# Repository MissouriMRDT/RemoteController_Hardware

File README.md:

# RemoteController_Hardware (Rev2_BuildTest)
This branch is for testing a new revision 2 build that removes the nodeMCU development board in place of a standalone ESP-12E, and replaces the LCD screen for an OLED.

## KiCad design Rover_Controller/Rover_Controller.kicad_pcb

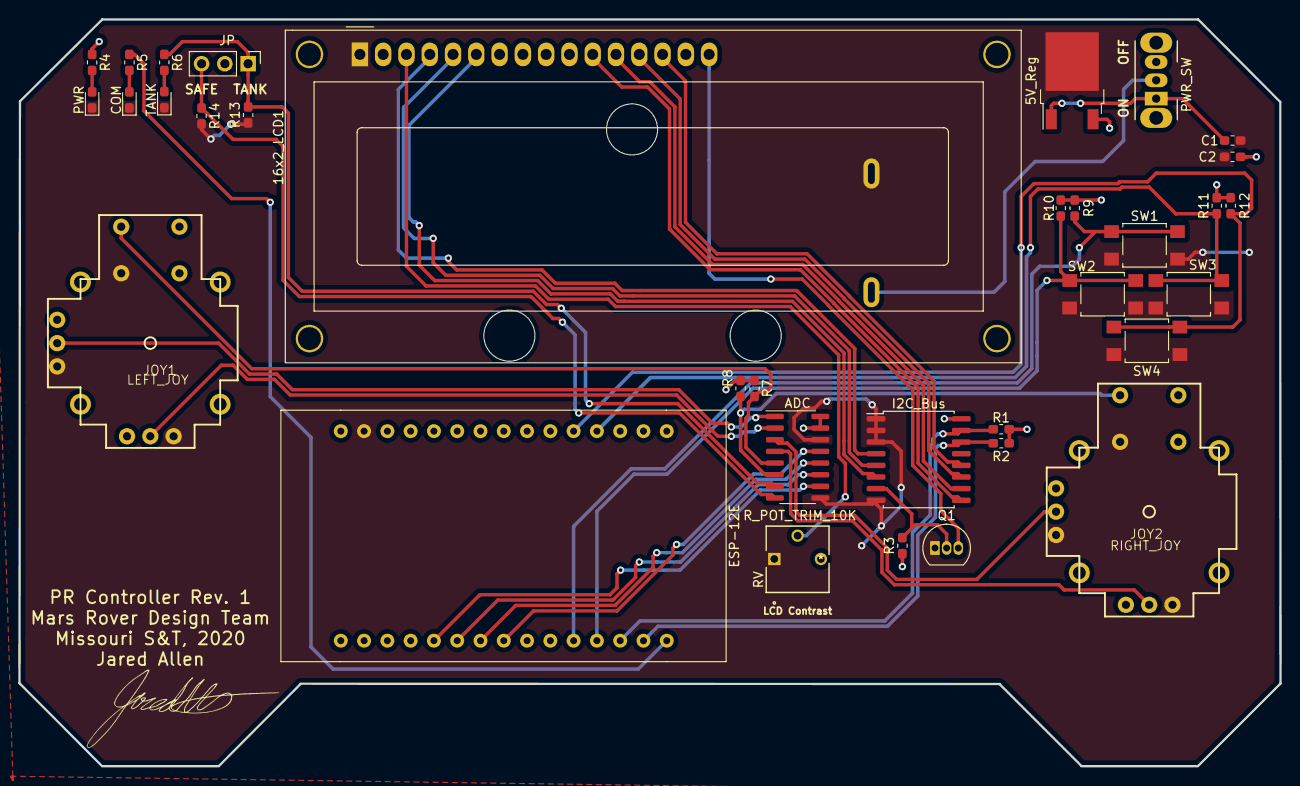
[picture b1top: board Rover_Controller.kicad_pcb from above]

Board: 2 copper layers, 137.6 x 81.5 mm, 35 parts (1 on the bottom side), 36 nets.

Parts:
5V_Reg: L7805; TO-252-2
16x2_LCD1: RC1602A; WC1602A
ADC: MCP3008; SOIC-16_3.9x9.9mm_P1.27mm
BT1: 9V_BAT; Battery_Holder_9V_BC9VPC-ND
C1, C2: 1uF; C_0603_1608Metric_Pad1.05x0.95mm_HandSolder
COM: BLUE; LED_0603_1608Metric_Pad1.05x0.95mm_HandSolder
ESP-12E: ESP8266_NodeMCU; ESP8266_nodeMCU
I2C_Bus: PCF8574; SOIC-16W_7.5x10.3mm_P1.27mm
JOY1: LEFT_JOY; JOYSTICK
JOY2: RIGHT_JOY; JOYSTICK
JP: Jumper_NC_Dual; PinHeader_1x03_P2.54mm_Vertical
PWR: GREEN; LED_0603_1608Metric_Pad1.05x0.95mm_HandSolder
PWR_SW: SW_SPDT; SW_CuK_OS102011MA1QN1_SPDT_Angled
Q1: S8050; TO-92_Inline
R1, R2, R3: 4.7K; R_0603_1608Metric_Pad1.05x0.95mm_HandSolder
R4, R5, R6: 510; R_0603_1608Metric_Pad1.05x0.95mm_HandSolder
R7, R8, R9, R10, R11, R12, R13, R14: 10K; R_0603_1608Metric_Pad1.05x0.95mm_HandSolder
RV: R_POT_TRIM_10K; 3362P-1-103LF
SW1, SW2, SW3, SW4: SW_Push; SW_SPST_TL3305A
TANK: RED; LED_0603_1608Metric_Pad1.05x0.95mm_HandSolder

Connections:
+5V: 5V_Reg.3, 16x2_LCD1.2, 16x2_LCD1.15, ADC.15, ADC.16, C2.1, ESP-12E.29, I2C_Bus.16, JOY1.H1, JOY1.V1, JOY2.H1, JOY2.V1, JP.2, R1.1, R2.1, R3.1, R4.1, R7.1, R8.1, R9.2, R10.2, R11.2, R12.2, RV.3
CLK: ADC.13, ESP-12E.16
CS: ADC.10, ESP-12E.22
D0: ESP-12E.2, R5.1
Din: ADC.11, ESP-12E.20
Dout: ADC.12, ESP-12E.18
GND: 5V_Reg.2, 16x2_LCD1.1, ADC.9, ADC.14, BT1.2, C1.2, C2.2, COM.1, ESP-12E.27, I2C_Bus.1, I2C_Bus.2, I2C_Bus.3, I2C_Bus.8, JOY1.B2A, JOY1.H3, JOY1.V3, JOY2.B2A, JOY2.H3, JOY2.V3, PWR.1, Q1.1, R13.1, R14.2, RV.1, SW1.2, SW2.2, SW3.2, SW4.2, TANK.1
LeftHorz: ADC.2, JOY1.H2
LeftSel: ADC.5, JOY1.B1A, R7.2
LeftVert: ADC.1, JOY1.V2
unnamed: 5V_Reg.1, C1.1, PWR_SW.1
unnamed: 16x2_LCD1.4, I2C_Bus.4
unnamed: 16x2_LCD1.5, I2C_Bus.5
unnamed: 16x2_LCD1.6, I2C_Bus.6
unnamed: 16x2_LCD1.11, I2C_Bus.9
unnamed: 16x2_LCD1.12, I2C_Bus.10
unnamed: 16x2_LCD1.13, I2C_Bus.11
unnamed: 16x2_LCD1.14, I2C_Bus.12
unnamed: BT1.1, PWR_SW.2
unnamed: COM.2, R5.2
unnamed: PWR.2, R4.2
unnamed: R6.2, TANK.2
P3: I2C_Bus.7, Q1.2, R3.2
RightHorz: ADC.4, JOY2.H2
RightSel: ADC.6, JOY2.B1A, R8.2
RightVert: ADC.3, JOY2.V2
SCL: ESP-12E.4, I2C_Bus.14, R2.2
SDA: ESP-12E.6, I2C_Bus.15, R1.2
SW1: ESP-12E.10, R9.1, SW1.1
SW2: ESP-12E.8, R10.1, SW2.1
SW3: ESP-12E.7, R11.1, SW3.1
SW4: ESP-12E.9, R12.1, SW4.1
SafeDrive: ADC.8, JP.3, R14.1
TankDrive: ADC.7, JP.1, R6.1, R13.2
V0: 16x2_LCD1.3, RV.2
k: 16x2_LCD1.16, Q1.3

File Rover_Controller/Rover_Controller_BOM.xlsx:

Id | Designator | Package | Quantity | Designation | Item Name | Part Number | Vendor | Cost Per Item | Cost | URL | Comments | Quantity
1 | R10,R7,R8,R12,R11,R9,R13,R14 | R_0603_1608Metric_Pad1.05x0.95mm_HandSolder | 8 | 10K |  |  |  |  |  |  |  |  |  | Total Cost
2 | BT1 | Battery_Holder_9V_BC9VPC-ND | 1 | 9V_BAT |  |  |  |  |  |  |  |  |  | 0
3 | R6,R5,R4 | R_0603_1608Metric_Pad1.05x0.95mm_HandSolder | 3 | 510
4 | I2C_Bus1 | SOIC-16W_7.5x10.3mm_P1.27mm | 1 | PCF8574
5 | R1,R2,R3 | R_0603_1608Metric_Pad1.05x0.95mm_HandSolder | 3 | 4.7K
6 | C2,C1 | C_0603_1608Metric_Pad1.05x0.95mm_HandSolder | 2 | 1uF
7 | ADC1 | SOIC-16_3.9x9.9mm_P1.27mm | 1 | MCP3008
8 | COM1 | LED_0603_1608Metric_Pad1.05x0.95mm_HandSolder | 1 | BLUE
9 | TANK1 | LED_0603_1608Metric_Pad1.05x0.95mm_HandSolder | 1 | RED
10 | JP1 | PinHeader_1x03_P2.54mm_Vertical | 1 | Jumper_NC_Dual
11 | 16x2_LCD1 | WC1602A | 1 | RC1602A
12 | JOY2 | JOYSTICK | 1 | RIGHT_JOY
13 | Q1 | TO-92_Inline | 1 | S8050
14 | JOY1 | JOYSTICK | 1 | LEFT_JOY
15 | ESP-12E1 | ESP8266_nodeMCU | 1 | ESP8266_NodeMCU
16 | PWR1 | LED_0603_1608Metric_Pad1.05x0.95mm_HandSolder | 1 | GREEN
17 | RV1 | 3362P-1-103LF | 1 | R_POT_TRIM_10K
18 | SW1,SW2,SW3,SW4 | SW_SPST_TL3305A | 4 | SW_Push
19 | PWR_SW1 | SW_CuK_OS102011MA1QN1_SPDT_Angled | 1 | SW_SPDT
20 | 5V_Reg_1 | TO-252-2 | 1 | L7805

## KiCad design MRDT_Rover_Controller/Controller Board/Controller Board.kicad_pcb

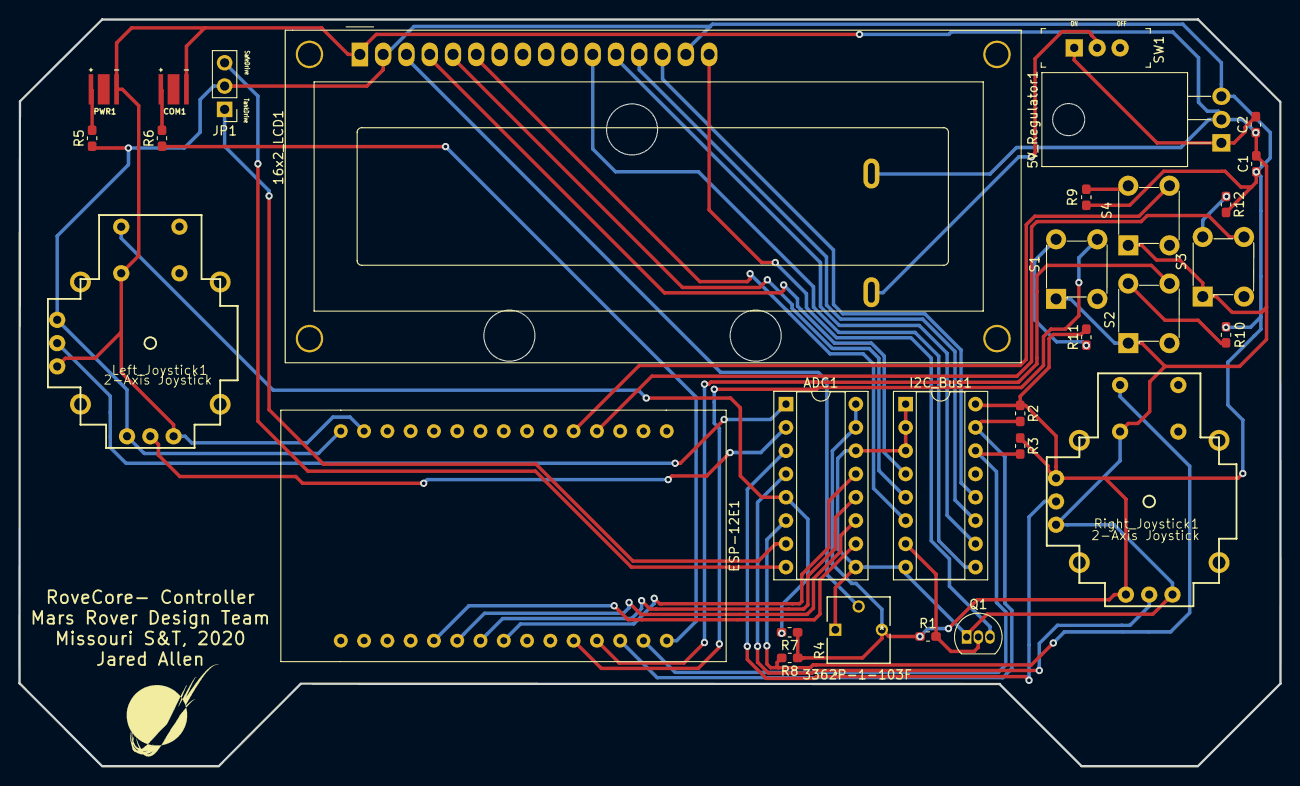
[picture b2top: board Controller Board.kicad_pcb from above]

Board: 2 copper layers, 137.6 x 81.5 mm, 31 parts (1 on the bottom side), 39 nets.

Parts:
5V_Regulator1: L7805; TO-220-3_Horizontal_TabDown
16x2_LCD1: RC1602A; WC1602A
ADC1: MCP3008; DIP-16_W7.62mm_Socket
BAT1: BC9VPC; Battery_Holder_9V_BC9VPC-ND
C1, C2: 1uF; C_0603_1608Metric_Pad1.05x0.95mm_HandSolder
COM1: BLUE; LED_CREE_XLAMP_XPG
ESP-12E1: ESP8266_NodeMCU; ESP8266_nodeMCU
I2C_Bus1: PCF8574; DIP-16_W7.62mm_Socket
JP1: Jumper_NC_Dual; PinHeader_1x03_P2.54mm_Vertical
Left_Joystick1: 2-Axis Joystick; JOYSTICK
PWR1: GREEN; LED_CREE_XLAMP_XPG
Q1: S8050; TO-92_Inline
R1, R2, R3: 4.7K; R_0603_1608Metric_Pad1.05x0.95mm_HandSolder
R4: 3362P-1-103F; 3362P-1-103LF
R5, R6: 100; R_0603_1608Metric_Pad1.05x0.95mm_HandSolder
R7, R8: 1K; R_0603_1608Metric_Pad1.05x0.95mm_HandSolder
R9, R10, R11, R12: 10K; R_0603_1608Metric_Pad1.05x0.95mm_HandSolder
Right_Joystick1: 2-Axis Joystick; JOYSTICK
S1, S2, S3, S4: 1825910-6; Switch_Tactile_THT_6x6mm
SW1: EG1218; Switch_Slide_11.6x4mm_EG1218

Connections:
5V: 5V_Regulator1.3, 16x2_LCD1.2, 16x2_LCD1.15, ADC1.15, ADC1.16, C1.1, ESP-12E1.29, I2C_Bus1.16, JP1.2, Left_Joystick1.H1, Left_Joystick1.V1, R1.1, R2.1, R3.1, R4.3, R5.1, R7.1, R8.1, R9.2, R10.2, R11.2, R12.2, Right_Joystick1.H1, Right_Joystick1.V1
/P3: I2C_Bus1.7, Q1.2, R1.2
/k: 16x2_LCD1.16, Q1.3
CLK: ADC1.13, ESP-12E1.16
CS: ADC1.10, ESP-12E1.22
D0: ESP-12E1.2, R6.1
Din: ADC1.11, ESP-12E1.20
Dout: ADC1.12, ESP-12E1.18
GND: 5V_Regulator1.2, 16x2_LCD1.1, ADC1.9, ADC1.14, BAT1.NEG, C1.2, C2.1, COM1.2, ESP-12E1.27, I2C_Bus1.1, I2C_Bus1.2, I2C_Bus1.3, I2C_Bus1.8, Left_Joystick1.B2A, Left_Joystick1.H3, Left_Joystick1.V3, PWR1.2, Q1.1, R4.1, Right_Joystick1.B2A, Right_Joystick1.H3, Right_Joystick1.V3, S1.1, S2.1, S3.1, S4.1
LFT_SEL: ADC1.5, Left_Joystick1.B1A, R7.2
LeftHorz: ADC1.2, Left_Joystick1.H2
LeftVert: ADC1.1, Left_Joystick1.V2
unnamed: 5V_Regulator1.1, C2.2, SW1.1
unnamed: 16x2_LCD1.4, I2C_Bus1.4
unnamed: 16x2_LCD1.5, I2C_Bus1.5
unnamed: 16x2_LCD1.6, I2C_Bus1.6
unnamed: 16x2_LCD1.11, I2C_Bus1.9
unnamed: 16x2_LCD1.12, I2C_Bus1.10
unnamed: 16x2_LCD1.13, I2C_Bus1.11
unnamed: 16x2_LCD1.14, I2C_Bus1.12
unnamed: BAT1.POS, SW1.2
unnamed: COM1.1, R6.2
unnamed: PWR1.1, R5.2
unnamed: R9.1, S4.2
unnamed: R10.1, S2.2
unnamed: R11.1, S1.2
unnamed: R12.1, S3.2
RGHT_SEL: ADC1.6, R8.2, Right_Joystick1.B1A
RightHorz: ADC1.4, Right_Joystick1.H2
RightVert: ADC1.3, Right_Joystick1.V2
SCL: ESP-12E1.4, I2C_Bus1.14, R3.2
SDA: ESP-12E1.6, I2C_Bus1.15, R2.2
SW1: ESP-12E1.10, S1.4
SW2: ESP-12E1.8, S2.4
SW3: ESP-12E1.7, S3.4
SW4: ESP-12E1.9, S4.4
SafeDrive: ADC1.8, JP1.3
TankDrive: ADC1.7, JP1.1
V0: 16x2_LCD1.3, R4.2

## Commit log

2019-09-21 Initial Schematic Files
    Initial KiCAD schematic with power power supply. 9V battery input voltage regulated down to 5v.
2019-09-21 Initial Schematic Files and Documentation
    New schematic file that only contains power supply, and initial documentation of project.
2019-09-22 Started ESP-nodeMCU footprint
2019-09-22 Footprint Drawing Completed
    Footprint and pads are correctly placed and outline. The pads do not correspond correctly to the esp in the schematic.
2019-09-28 MCU block edited, i2c and lcd added
2019-09-28 I2C and LCD connections
2019-09-28 Documentation Updated
2019-09-28 I2C to LCD Initial Completion
2019-09-28 I2C to LCD Connection Updated
2019-09-28 Joystick Symbol Created
    NodeMCU symbol updated
2019-09-28 Joystick Library Imported
2019-09-28 Joystick Schematic Placement
    Changed joystick placement and provided power.
2019-09-28 Updated Controller Documentation
2019-10-03 Joystick Wires Placed
2019-10-03 Reorganization of Joystick Library
    No change to circuit design or PCB
2019-10-05 Started Joystick Connections to ESP
2019-10-05 Multiplexer Connected to Joysticks
    Temporary design where joysticks are connected to ESP using 4051 Multiplexer
2019-10-05 Replaced Multiplexer with ADC
    MCP3008 10-bit ADC connected with Joysticks and ESP. All Critical components are added to the schematic at this time.
2019-10-08 Jumper Added
2019-10-08 I2C Bus Footprint Created
    Additional footprints added
2019-10-08 Updated all major Footprints
2019-10-08 Potentiometer Changed
    Changed potentiometer to footprint from Bourns EDA library. 10Kohm potentiometer added.
2019-10-08 Footprints Aded
    Footprints for all current components have been added, began work on the PCB.
2019-10-08 LED Indicators Added
    Power LED indicator, and connectivity LED indicator added.
2019-10-09 Updated Footprints
2019-10-09 Updated ESP Footprint
2019-10-09 Schematic Placement Changes
2019-10-09 Footprint Repaird for ESP
    Due to changes in file placement for ESP, the symbol needed to be updated in order to work with the footprint.
2019-10-09 PCB Design Started
    Created Controller outline in AutoCAD, placed most components on the board.
2019-10-09 Update fp-info-cache
2019-10-10 gitignore updated
2019-10-10 Fixed Empty Pins
    Corrected areas of the schematic for pins that have no use
2019-10-10 Added Pull-Up Resistors to ADC
2019-10-10 Updated Layout of PCB
2019-10-10 Added 4 THT PushButtons
2019-10-10 9v Battery Holder Added
2019-10-10 Updated Net, and Started PCB Traces
2019-10-10 PCB Traces Updated
    Traces connected to right joystick and pushbuttons
2019-10-10 Trace Update
2019-10-11 PCB Traces Updated
2019-10-11 PCB Updated
2019-10-11 PCB Updated, Power Switch Added
2019-10-11 I2C Traces Placed
2019-10-11 All I2C Traces Placed
2019-10-11 PCB Updated
    Team Lead approved design at this point.
2019-10-12 All PCB Traces Placed
2019-10-12 3D Models added to components
2019-10-12 3D Components Finalized
    PDR ready at this point
2019-10-12 MRDT Silkscreen added
2019-10-12 Silkscreen Updated with MRDT Logo
2019-10-18 Symbol Updates
2019-11-03 Capactiro Added to Input of 7805
2019-11-03 Silkscreen Updated
    Capactior connections made with new capactior at input of 7805, and silkscreen updated.
2019-11-03 Silkscreen Updated
2019-11-03 7805 Input Capacitor Updated
2019-11-03 Netlist Updated
2019-11-03 Silkscreen Updated for LEDs
2019-11-05 Added Test Code
    Also reorganized some files related to PDR
2019-11-05 Revision 2 Files Added
2019-11-05 Code Libraries and LCD Updated
2019-11-05 All Push-Buttons Re-Mapped
    Buttons 3 & 4 had to be re-mapped through the ADC due to compatability issues with the original pins they were connected to. All schematic and PCB changes have been made. Buttons 1 & 2 also needed to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
2019-11-05 Button Resistor Connections Changed
    Re-configuration to resistors connected to push buttons. Changes made for both schematic and PCB. All new traces placed.
2019-11-06 Test Code Modifications
2019-11-07 removed duplicated files
2019-11-07 Button Layout Changed
    Drive control jumper and button layout has changed due to testing errors found. The jumper will now run through the ADC, whereas all 4 buttons will all run through the ESP directly. This version does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
2019-11-07 Push Button and Jumper PCB Traces Updated
2019-11-07 PushButtons Tied-HIGH
2019-11-07 New Button Traces Placed
2019-11-10 3D Files Updated
2019-11-10 Trace corners re-adjusted
2019-11-10 Notes Doc Updated
2019-11-11 Repository Re-Organized
2019-11-11 Power Regulator and LEDs re-configured
    Power regulator and LEDs for power and COM indication have been re-done in the shematic on the 50mil grid size
2019-11-11 LCD Schematic re-configured
    re-configured to fit 50mil grid
2019-11-11 Footprints Given in Power Supply/LCD
2019-11-12 ADC Re-Mapped on Schematic
2019-11-12 Push Buttons Re-Mapped and Changed to 2-Pin SPST
2019-11-12 Schematic Re-Done on 50mil Grid
    The entire schematic has been re-formatted on a 50mil grid, along with a few other changes as outlined in the Documentation file "Board Review Notes"
2019-11-14 re-mapped joysticks
2019-11-14 PCF and MCP Switched to SMD
2019-11-14 File Name Change
2019-11-14 MCP3008 SMD Footprint Applied
2019-11-16 Footrpints Updated
2019-11-16 PCB Netlist Updated
2019-11-19 Traces Removed From PCB
    Traces were removed so that re-tracing could be done. With a few new SMD components and enhanced component placement re-tracing the whole board was deemed appropriate.
2019-11-19 Display Association Changed
2019-11-19 Components Re-Configured on PCB
2019-11-28 PCB Components Re-Alligned
2019-12-03 Traces Updated
2019-12-03 I2C Bus Traces Completed
2019-12-04 All Traces Placed
2019-12-04 Datasheets Added
2019-12-05 Re-Traced Long Diagonal Traces
2019-12-05 Button Footprints Updated
2019-12-10 5V PCB Trace Pads Updated
2019-12-10 Slide Switch Changed to Angled Switch
2019-12-10 Schematic Updated for Switch
2019-12-10 7805 Package Updated
2019-12-10 BOM Added
2019-12-11 BOM Updated
2019-12-11 BOM and Signature Updated
2019-12-11 Signature File Location Changed
2019-12-11 Libraries Updated & PCB Silkscreen Updated
2019-12-11 ESP Library Updated
2019-12-11 Update Rover_Controller.sch-bak
2019-12-11 3D Models Added
2020-01-25 Test Code Updated
2020-01-26 ESP12 Documentation Added
2020-01-26 Code Libraries Updated
2020-01-27 Main Code Updated
    Included screen test to display joystick ADC values on LCD after startup
2020-02-04 LCD Menu Added
2020-03-04 ESP-12E Added
2020-03-05 Added 3V3 Regulator, Removed Unused Libraries
2020-03-05 Connected ESP-12E Ports
2020-03-09 Created New Controller Outline
